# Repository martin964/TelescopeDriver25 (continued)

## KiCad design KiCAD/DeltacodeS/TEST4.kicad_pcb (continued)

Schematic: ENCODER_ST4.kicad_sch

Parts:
C27, C62, C63: 100n; C_1206
P6, P7: CONN_ENCODER; Conn_Modular_4
P11: CONN_ST4; Conn_Modular_6
Q3, Q4: DDC143ZU; SOT-363
R3, R7, R22, R23: 270R; R_1206
R18, R19, R20, R21: 10K; R_1206
R24, R25, R26, R27: 2K; R_1206
R28, R29, R30, R31: 220R; R_1206
U10: ACSL-6400; SO-16-N
U13: ACPL-247; SO-16-N
U14: DCDC_SIL; SIL_DCDC_4Pin
W12: PIN_ENC_RA; TestPad_09mmDrill
W13: PIN_ENC_DA; TestPad_09mmDrill
W14: PIN_ST4_W; TestPad_09mmDrill
W15: PIN_ST4_N; TestPad_09mmDrill
W16: PIN_ST4_S; TestPad_09mmDrill
W17: PIN_ST4_E; TestPad_09mmDrill
W18: PIN_ENC_RB; TestPad_09mmDrill
W19: PIN_ENC_DB; TestPad_09mmDrill

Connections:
+5V: U14.1 (Vin); also elsewhere on the board
ENC_DEC_CHA: R26.2, U10.12, W13.1; also elsewhere on the board
ENC_DEC_CHB: R27.2, U10.11, W19.1; also elsewhere on the board
ENC_RA_CHA: R24.2, U10.14, W12.1; also elsewhere on the board
ENC_RA_CHB: R25.2, U10.13, W18.1; also elsewhere on the board
GND: C27.2, U10.9 (GND), U10.16 (GND), U13.9, U13.11, U13.13, U13.15, U14.2 (GND); also elsewhere on the board
unnamed: C62.1, C63.1, P6.2 (+5V), P7.2 (+5V), R3.1, R7.1, R22.1, R23.1, R28.1, R29.1, R30.1, R31.1, U14.4 (V+)
unnamed: C62.2, C63.2, P6.4 (GND), P7.4 (GND), P11.2 (GND), Q3.1 (B), Q3.4, Q4.1 (B), Q4.4, U14.3 (V-)
unnamed: P6.1 (CHB), Q3.2 (E)
unnamed: P6.3 (CHA), Q3.5
unnamed: P7.1 (CHB), Q4.2 (E)
unnamed: P7.3 (CHA), Q4.5
unnamed: P11.3 (+RA), U13.8
unnamed: P11.4 (+DEC), U13.6
unnamed: P11.5 (-DEC), U13.4
unnamed: P11.6 (-RA), U13.2
unnamed: Q3.3 (C), U10.2
unnamed: Q3.6, U10.4
unnamed: Q4.3 (C), U10.6
unnamed: Q4.6, U10.8
unnamed: R3.2, U10.7
unnamed: R7.2, U10.5
unnamed: R22.2, U10.3
unnamed: R23.2, U10.1
unnamed: R28.2, U13.7
unnamed: R29.2, U13.5
unnamed: R30.2, U13.3
unnamed: R31.2, U13.1
ST4_E_RA+: R21.2, U13.10, W17.1; also elsewhere on the board
ST4_N_DEC+: R20.2, U13.12, W15.1; also elsewhere on the board
ST4_S_DEC-: R19.2, U13.14, W16.1; also elsewhere on the board
ST4_W_RA-: R18.2, U13.16, W14.1; also elsewhere on the board

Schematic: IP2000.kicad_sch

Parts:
C42, C60, C61, C69, C71: 100n; C_1206
P10: ENCODERMODUL; IP2000_Modul
R38: 50k; R_1206
U12: MAX3379E; TSSOP-14_4.4x5mm_Pitch0.65mm
U20: MAX3391E; TSSOP-14_4.4x5mm_Pitch0.65mm

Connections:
+5V: C60.1, C61.1, C69.2, P10.7 (+5V), U12.14 (VCC), U20.14 (VCC); also elsewhere on the board
GND: C42.1, C60.2, C61.2, C69.1, C71.1, P10.5 (GND), P10.6 (GND), R38.1, U12.5 (I_VL4), U12.7 (GND), U20.7 (GND); also elsewhere on the board
IP2000_ERR: U20.3 (O_VL2); also elsewhere on the board
IP2000_MISO: U20.2 (O_VL1); also elsewhere on the board
IP2000_MOSI: U12.2 (I_VL1); also elsewhere on the board
IP2000_OE: R38.2, U12.8 (THREE-STATE), U20.8 (THREE-STATE); also elsewhere on the board
IP2000_RES: U12.4 (I_VL3); also elsewhere on the board
IP2000_SCK: U20.5 (I_VL4); also elsewhere on the board
IP2000_SEN: U12.3 (I_VL2); also elsewhere on the board
IP2000_TRG: U20.4 (I_VL3); also elsewhere on the board
unnamed: P10.1 (MISO), U20.13 (I_VCC1)
unnamed: P10.2 (MOSI), U12.13 (O_VCC1)
unnamed: P10.3 (SEN), U12.12 (O_VCC2)
unnamed: P10.4 (SCK), U20.10 (O_VCC4)
unnamed: P10.8 (TRG), U20.11 (O_VCC3)
unnamed: P10.9 (ERR), U20.12 (I_VCC2)
unnamed: P10.10 (RES), U12.11 (O_VCC3)

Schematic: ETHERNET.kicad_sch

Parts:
C47, C48, C50, C51, C52, C53, C57: 100n; C_1206
C49: 4.7µ50V; C_1206
C54: 2.2µ 50V; C_1206
C56: 22p; C_1206
C58, C59: 10µ25V; C_1206
J2: RJ45-TRANSFO; RJ45_TRANSFO_CONNEX_11AC010X
L4: 120; C_1207_Reflow
R14: 6k49; R_0805
R15, R16, R32: 1k; R_1206
R17, R34, R36: 10k; R_1206
R33: 1k5; R_1206
R35: 39R; R_1206
U11: KSZ8081RNA; QFN-24-1EP_4x4mm_Pitch0.5mm
W22: PIN_PHY_MDIO; TestPad_09mmDrill
W23: PIN_PHY_MDC; TestPad_09mmDrill
W24: PIN_PHY_REFCLK; TestPad_09mmDrill
W25: PIN_PHY_TXD1; TestPad_09mmDrill
W26: PIN_PHY_INTRP; TestPad_09mmDrill
W27: PIN_PHY_RXERR; TestPad_09mmDrill
W28: PIN_PHY_TXD0; TestPad_09mmDrill
W29: PIN_PHY_RXD0; TestPad_09mmDrill
W30: PIN_PHY_CRS_DV; TestPad_09mmDrill
W31: PIN_PHY_TXEN; TestPad_09mmDrill
W32: PIN_PHY_RESET; TestPad_09mmDrill
W33: PIN_PHY_RXD1; TestPad_09mmDrill
Y2: 25MHz; TCXO_53

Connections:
GND: C47.2, C48.2, C49.2, C50.2, C51.2, C52.2, C53.2, C54.2, C56.2, C57.2, C58.2, C59.2, J2.8, R14.2, R34.2, U11.22 (GND), U11.25 (GND), Y2.2 (GND); also elsewhere on the board
unnamed: C47.1, J2.2 (TCT)
unnamed: C48.1, J2.5 (RCT)
unnamed: C49.1, C50.1, C51.1, L4.2, U11.2 (VDDA_3V3)
unnamed: C52.1, C54.1, U11.1 (VDD_1V2)
unnamed: C56.1, R14.1, U11.9 (REXT)
unnamed: J2.1 (TD+), U11.6 (TXP)
unnamed: J2.3 (TD-), U11.5 (TXM)
unnamed: J2.4 (RD+), U11.4 (RXP)
unnamed: J2.6 (RD-), U11.3 (RXM)
unnamed: J2.GA (LEDG_A), R32.2
unnamed: J2.GK (LEDG_K), R36.2, U11.23 (LED0/ANEN_SPEED)
unnamed: J2.YA (LEDY_A), R16.2
unnamed: R35.2, U11.16 (REF_CLK), W24.1
unnamed: U11.8 (XI), Y2.3 (OUT)
PHY_CRS_DV: R34.1, U11.15 (CRS_DV/PHYAD[1,0]), W30.1; also elsewhere on the board
PHY_INTRP: R15.2, U11.18 (INTRP), W26.1; also elsewhere on the board
PHY_LED_Y: J2.YK (LEDY_K); also elsewhere on the board
PHY_MDC: U11.11 (MDC), W23.1; also elsewhere on the board
PHY_MDIO: R33.2, U11.10 (MDIO), W22.1; also elsewhere on the board
PHY_REFCLK: R35.1; also elsewhere on the board
PHY_RESET: C59.1, R17.1, U11.24 (~RST), W32.1; also elsewhere on the board
PHY_RXD0: U11.13 (RXD0), W29.1; also elsewhere on the board
PHY_RXD1: U11.12 (RXD1), W33.1; also elsewhere on the board
PHY_RXERR: U11.17 (RXER), W27.1; also elsewhere on the board
PHY_TXD0: U11.20 (TXD0), W28.1; also elsewhere on the board
PHY_TXD1: U11.21 (TXD1), W25.1; also elsewhere on the board
PHY_TXEN: U11.19 (TXEN), W31.1; also elsewhere on the board

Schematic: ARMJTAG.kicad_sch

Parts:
C68: 100n; C_1206
P9, P21: CONN_01X03; Pin_Header_Straight_1x03
P20: CORTEX_DBG; box_header_2x5x2.54_straight
R45, R46, R47, R51: 100k; R_1206

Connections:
DEBUG_DETECT: P20.9 (DETECT), R51.2; also elsewhere on the board
DEBUG_RESET: P20.10 (nRESET), R47.2; also elsewhere on the board
DEBUG_RXD: P9.2; also elsewhere on the board
DEBUG_SWCLK: P20.4 (SWDCLK), R46.2; also elsewhere on the board
DEBUG_SWDIO: P20.2 (SWDIO), R45.2; also elsewhere on the board
DEBUG_SWO: P20.6 (SWO); also elsewhere on the board
DEBUG_TXD: P21.2; also elsewhere on the board
GND: C68.2, P20.3 (GND), P20.5 (GND); also elsewhere on the board
MAX232_R2OUT: P9.3; also elsewhere on the board
MAX232_T2IN: P21.3; also elsewhere on the board
unnamed: P20.7 (TXD), P21.1
unnamed: P9.1, P20.8 (RXD)

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
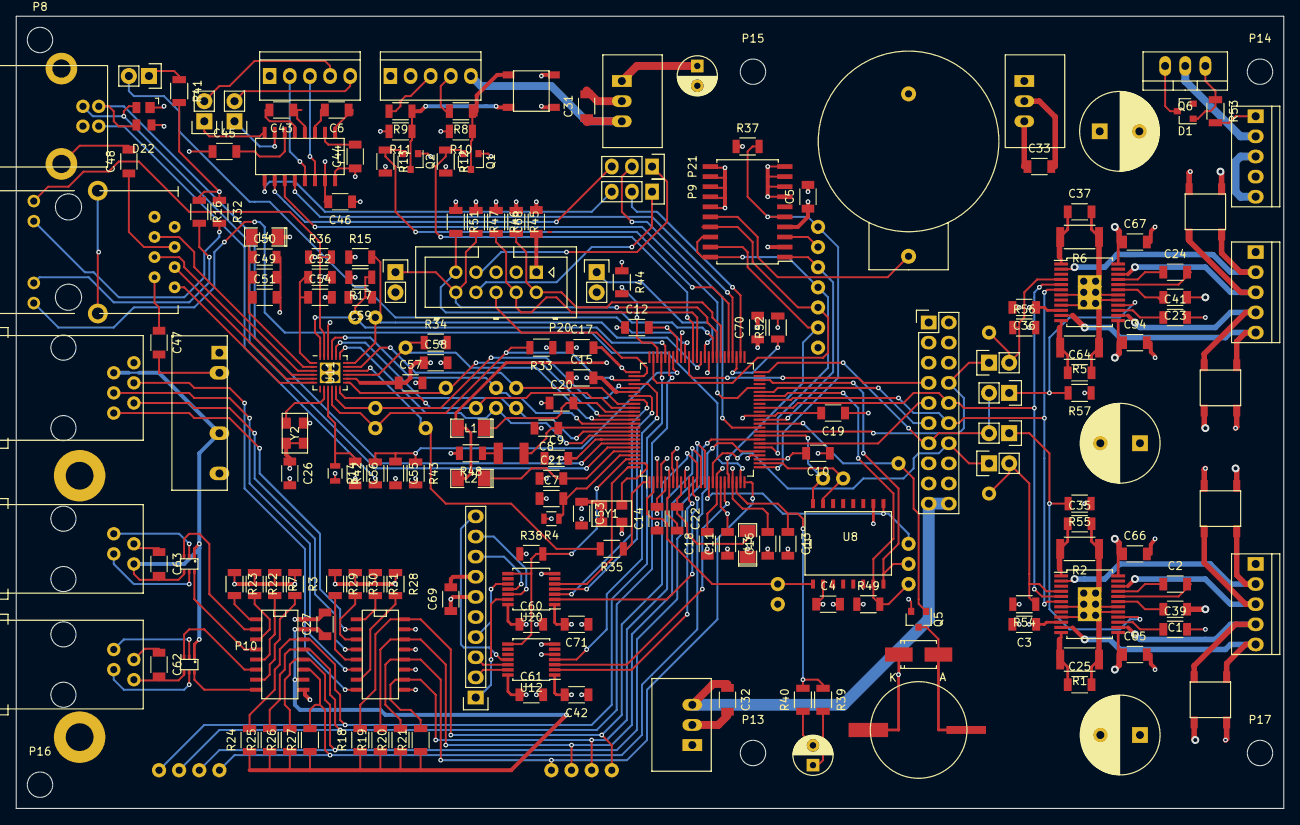
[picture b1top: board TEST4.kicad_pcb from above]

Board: 4 copper layers, 160.0 x 100.0 mm, 232 parts (0 on the bottom side), 176 nets.

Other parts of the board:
C1, C2, C39: 220n; C_1206
C3, C25, C34, C35, C66: 100n; C_1206
C40: 100µ50V; C_Radial_D10_L13_P5
P3: CONN_STEPPER; Pin_Header_Straight_LForm_1x05
R1, R2: 0,167; R_2010
U1: A3992; SSOP24_A3992_Pitch0.65mm

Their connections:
+24V: C1.1, C34.1, C40.1, C66.1, U1.13, U1.24; also elsewhere on the board
GND: C3.2, C25.2, C34.2, C35.2, C39.2, C40.2, C66.2, P3.1, R1.1, R2.1, U1.7, U1.9, U1.17, U1.18, U1.25, U1.26, U1.27, U1.28, U1.29, U1.30; also elsewhere on the board
unnamed: C1.2, U1.19
unnamed: C2.1, U1.21
unnamed: C2.2, U1.20
unnamed: C25.1, R1.2, U1.12
unnamed: C35.1, R2.2, U1.1
unnamed: C39.1, U1.15
SPI0_CLK: U1.5; also elsewhere on the board
SPI0_MOSI: U1.6; also elsewhere on the board

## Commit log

2025-03-16 CPU symbol changed, all pins on one page
